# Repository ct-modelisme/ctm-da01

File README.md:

# CTM-DA01: Digital Sound Decoder 01

The CTM-DA01 is a sound module for modelrailway projects.
This sound module is compatible with DCC & DC train layouts.

## Licenses

The hardware is released under OpenHardware principes, and the software under OpenSource principes.

 - Hardware (PCB): [Creative Commons Attribution-ShareAlike 4.0 International License](http://creativecommons.org/licenses/by-sa/4.0/)
 - Software (Firmware): [GNU General Public License v3](https://www.gnu.org/licenses/)

## Current releases

 - Hardware (PCB): version 1.0
 - Software (Firmware): version 1.1

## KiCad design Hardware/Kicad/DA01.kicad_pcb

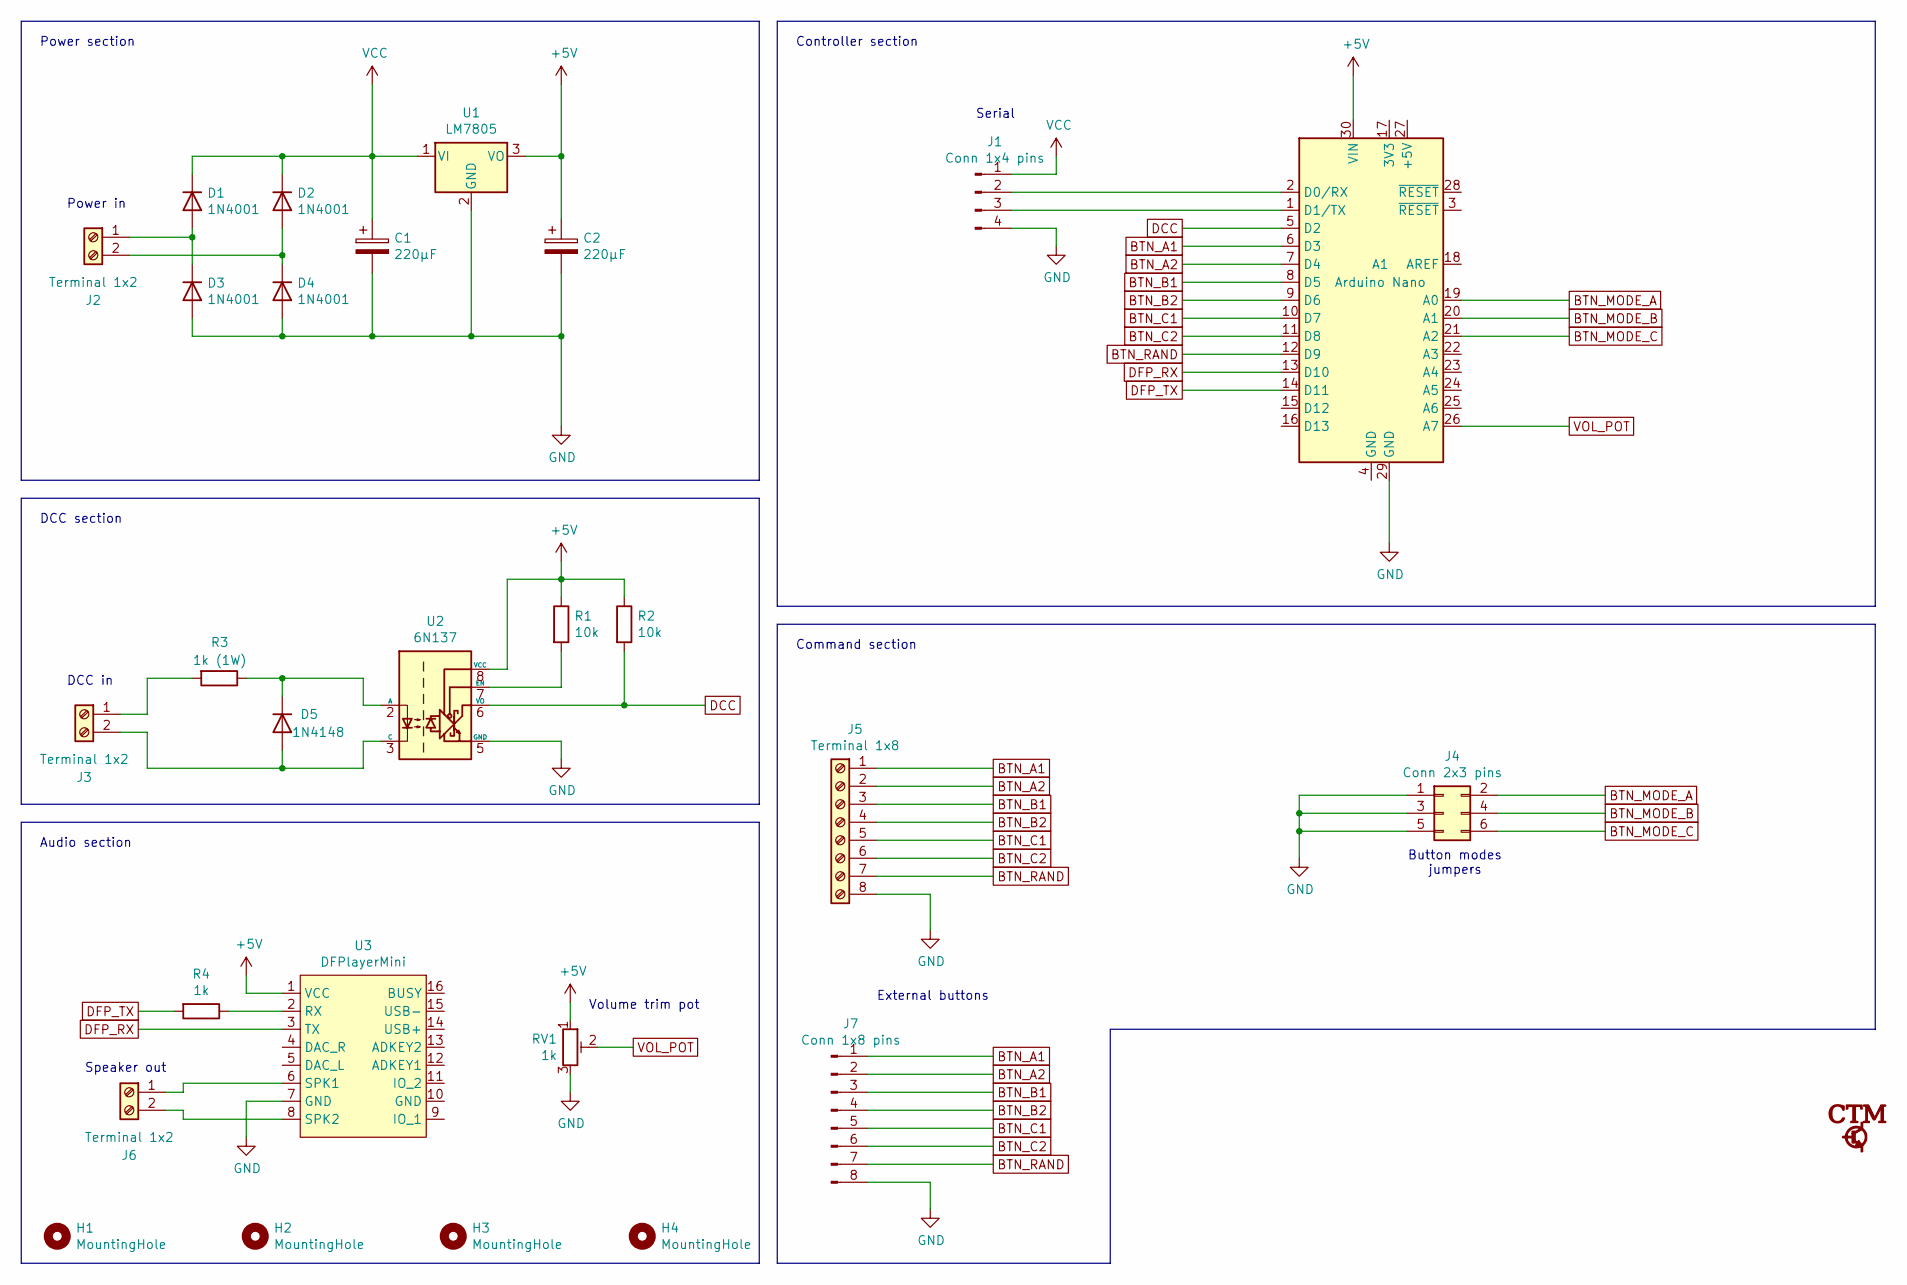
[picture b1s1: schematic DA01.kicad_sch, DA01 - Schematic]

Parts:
A1: Arduino Nano; Arduino_Nano
C1, C2: 220µF; CP_Radial_D6.3mm_P2.50mm
D1, D2, D3, D4: 1N4001; D_DO-41_SOD81_P10.16mm_Horizontal
D5: 1N4148; D_DO-35_SOD27_P7.62mm_Horizontal
H1, H2, H3, H4: MountingHole; MountingHole_3.2mm_M3
J1: Conn 1x4 pins; PinHeader_1x04_P2.54mm_Vertical
J2, J3, J6: Terminal 1x2; TerminalBlock_bornier-2_P5.08mm
J4: Conn 2x3 pins; PinHeader_2x03_P2.54mm_Vertical
J5: Terminal 1x8; TerminalBlock_bornier-8_P5.08mm
J7: Conn 1x8 pins; PinHeader_1x08_P2.54mm_Vertical
R1, R2: 10k; R_Axial_DIN0207_L6.3mm_D2.5mm_P10.16mm_Horizontal
R3: 1k (1W); R_Axial_DIN0309_L9.0mm_D3.2mm_P12.70mm_Horizontal
R4: 1k; R_Axial_DIN0207_L6.3mm_D2.5mm_P10.16mm_Horizontal
RV1: 1k; Potentiometer_ACP_CA9-H2,5_Horizontal
U1: LM7805; TO-220-3_Vertical
U2: 6N137; DIP-8_W7.62mm
U3: DFPlayerMini; DFRobot_DFPlayerMini_DFR0299

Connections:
+5V: A1.30 (VIN), C2.1, R1.1, R2.1, RV1.1, U1.3 (VO), U2.8 (VCC), U3.1 (VCC)
BTN_A1: A1.6 (D3), J5.1, J7.1
BTN_A2: A1.7 (D4), J5.2, J7.2
BTN_B1: A1.8 (D5), J5.3, J7.3
BTN_B2: A1.9 (D6), J5.4, J7.4
BTN_C1: A1.10 (D7), J5.5, J7.5
BTN_C2: A1.11 (D8), J5.6, J7.6
BTN_MODE_A: A1.19 (A0), J4.2
BTN_MODE_B: A1.20 (A1), J4.4
BTN_MODE_C: A1.21 (A2), J4.6
BTN_RAND: A1.12 (D9), J5.7, J7.7
DCC: A1.5 (D2), R2.2, U2.6 (VO)
DFP_RX: A1.13 (D10), U3.3 (TX)
DFP_TX: A1.14 (D11), R4.2
GND: A1.29 (GND), C1.2, C2.2, D3.2 (A), D4.2 (A), J1.4, J4.1, J4.3, J4.5, J5.8, J7.8, RV1.3, U1.2 (GND), U2.5 (GND), U3.7 (GND)
unnamed: A1.1 (D1/TX), J1.3
unnamed: A1.2 (D0/RX), J1.2
unnamed: D1.2 (A), D3.1 (K), J2.1
unnamed: D2.2 (A), D4.1 (K), J2.2
unnamed: D5.1 (K), R3.1, U2.2 (A)
unnamed: D5.2 (A), J3.2, U2.3 (C)
unnamed: J3.1, R3.2
unnamed: J6.1, U3.6 (SPK1)
unnamed: J6.2, U3.8 (SPK2)
unnamed: R1.2, U2.7 (EN)
unnamed: R4.1, U3.2 (RX)
VCC: C1.1, D1.1 (K), D2.1 (K), J1.1, U1.1 (VI)
VOL_POT: A1.26 (A7), RV1.2

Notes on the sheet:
Volume trim pot
DCC in
Power section
DCC section
Button modes jumpers
Command section
Serial
Power in
Speaker out
Audio section
External buttons
Controller section

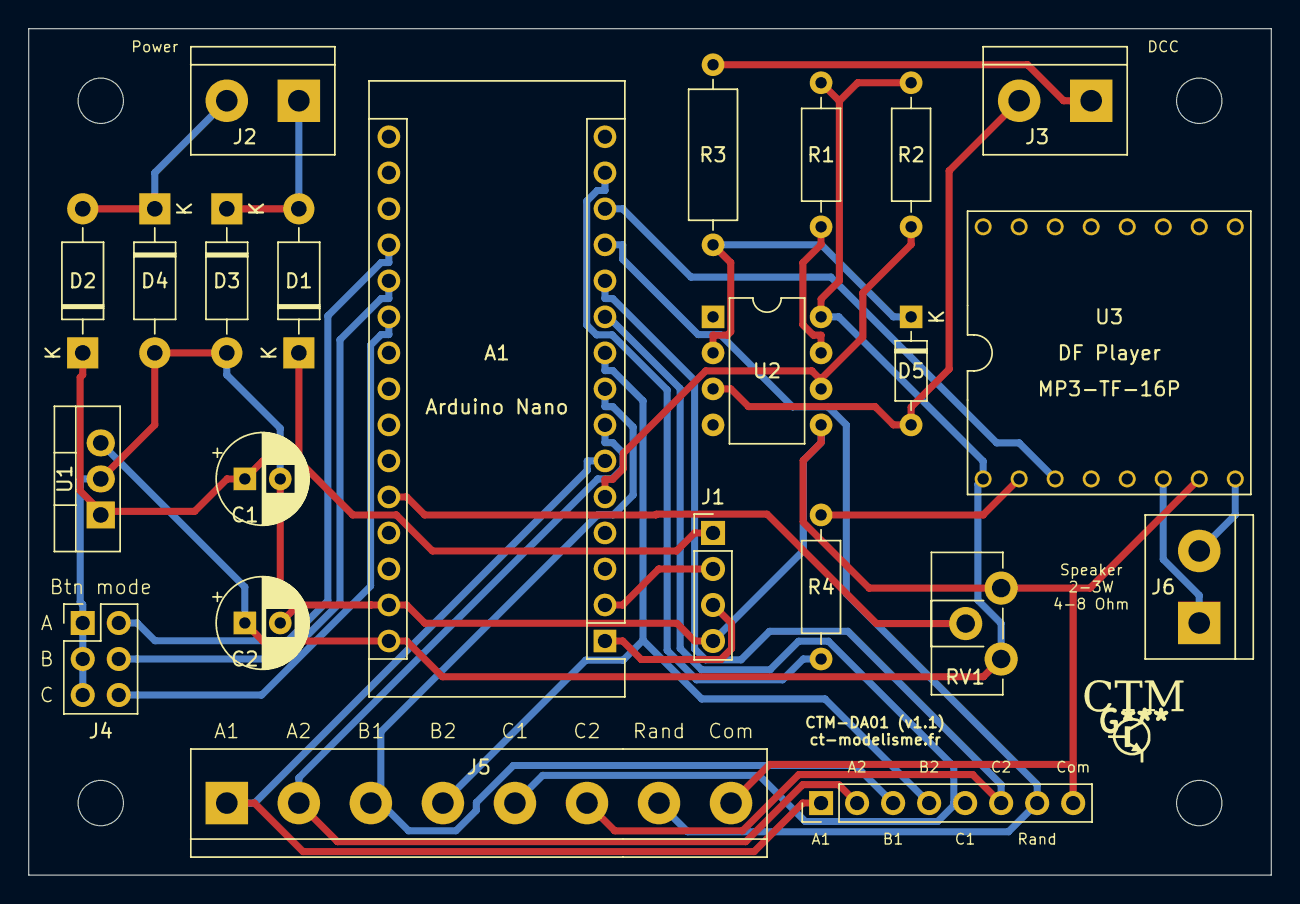
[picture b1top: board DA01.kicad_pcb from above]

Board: 2 copper layers, 87.6 x 59.7 mm, 27 parts (0 on the bottom side), 28 nets.

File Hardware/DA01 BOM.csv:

"Source:","/home/iwa/documents/KiCAD/Digital Accessory Decoder/DAD 02/DAD 02/DAD 02.sch"
"Date:","Mon 23 Aug 2021 12:42:14 PM CEST"
"Tool:","Eeschema 5.1.10"
"Generator:","/usr/share/kicad/plugins/bom_csv_grouped_by_value.py"
"Component Count:","27"

"Individual Components:"

"Item","Qty","Reference(s)","Value","LibPart","Footprint","Datasheet"
"","","A1","Arduino Nano","MCU_Module:Arduino_Nano_v2.x","Module:Arduino_Nano","https://www.arduino.cc/en/uploads/Main/ArduinoNanoManual23.pdf"
"","","C1","220µF","Device:C_Polarized","Capacitor_THT:CP_Radial_D6.3mm_P2.50mm","~"
"","","C2","220µF","Device:C_Polarized","Capacitor_THT:CP_Radial_D6.3mm_P2.50mm","~"
"","","D1","1N4001","Diode:1N4001","Diode_THT:D_DO-41_SOD81_P10.16mm_Horizontal","http://www.vishay.com/docs/88503/1n4001.pdf"
"","","D2","1N4001","Diode:1N4001","Diode_THT:D_DO-41_SOD81_P10.16mm_Horizontal","http://www.vishay.com/docs/88503/1n4001.pdf"
"","","D3","1N4001","Diode:1N4001","Diode_THT:D_DO-41_SOD81_P10.16mm_Horizontal","http://www.vishay.com/docs/88503/1n4001.pdf"
"","","D4","1N4001","Diode:1N4001","Diode_THT:D_DO-41_SOD81_P10.16mm_Horizontal","http://www.vishay.com/docs/88503/1n4001.pdf"
"","","D5","1N4148","Diode:1N4148","Diode_THT:D_DO-35_SOD27_P7.62mm_Horizontal","https://assets.nexperia.com/documents/data-sheet/1N4148_1N4448.pdf"
"","","H1","MountingHole","Mechanical:MountingHole","MountingHole:MountingHole_3.2mm_M3","~"
"","","H2","MountingHole","Mechanical:MountingHole","MountingHole:MountingHole_3.2mm_M3","~"
"","","H3","MountingHole","Mechanical:MountingHole","MountingHole:MountingHole_3.2mm_M3","~"
"","","H4","MountingHole","Mechanical:MountingHole","MountingHole:MountingHole_3.2mm_M3","~"
"","","J1","Conn 1x4 pins","Connector:Conn_01x04_Male","Connector_PinHeader_2.54mm:PinHeader_1x04_P2.54mm_Vertical","~"
"","","J2","Terminal 1x2","Connector:Screw_Terminal_01x02","TerminalBlock:TerminalBlock_bornier-2_P5.08mm","~"
"","","J3","Terminal 1x2","Connector:Screw_Terminal_01x02","TerminalBlock:TerminalBlock_bornier-2_P5.08mm","~"
"","","J4","Conn 2x3 pins","Connector_Generic:Conn_02x03_Odd_Even","Connector_PinHeader_2.54mm:PinHeader_2x03_P2.54mm_Vertical","~"
"","","J5","Terminal 1x8","Connector:Screw_Terminal_01x08","TerminalBlock:TerminalBlock_bornier-8_P5.08mm","~"
"","","J6","Terminal 1x2","Connector:Screw_Terminal_01x02","TerminalBlock:TerminalBlock_bornier-2_P5.08mm","~"
"","","J7","Conn 1x8 pins","Connector:Conn_01x08_Male","Connector_PinHeader_2.54mm:PinHeader_1x08_P2.54mm_Vertical","~"
"","","R1","10k","Device:R","Resistor_THT:R_Axial_DIN0207_L6.3mm_D2.5mm_P10.16mm_Horizontal","~"
"","","R2","10k","Device:R","Resistor_THT:R_Axial_DIN0207_L6.3mm_D2.5mm_P10.16mm_Horizontal","~"
"","","R3","1k (1W)","Device:R","Resistor_THT:R_Axial_DIN0309_L9.0mm_D3.2mm_P12.70mm_Horizontal","~"
"","","R4","1k","Device:R","Resistor_THT:R_Axial_DIN0207_L6.3mm_D2.5mm_P10.16mm_Horizontal","~"
"","","RV1","1k","Device:R_Potentiometer_Trim","Potentiometer_THT:Potentiometer_ACP_CA9-H2,5_Horizontal","~"
"","","U1","LM7805","Regulator_Linear:LM7805_TO220","Package_TO_SOT_THT:TO-220-3_Vertical","https://www.onsemi.cn/PowerSolutions/document/MC7800-D.PDF"
"","","U2","6N137","Isolator:6N137","Package_DIP:DIP-8_W7.62mm","https://docs.broadcom.com/docs/AV02-0940EN"
"","","U3","DFPlayerMini","DAD-02-rescue:DFPlayerMini-Audio","Module:DFRobot_DFPlayerMini_DFR0299","https://wiki.dfrobot.com/DFPlayer_Mini_SKU_DFR0299"



"Collated Components:"

"Item","Qty","Reference(s)","Value","LibPart","Footprint","Datasheet"
"1","1","A1","Arduino Nano","MCU_Module:Arduino_Nano_v2.x","Module:Arduino_Nano","https://www.arduino.cc/en/uploads/Main/ArduinoNanoManual23.pdf"
"2","2","C1, C2","220µF","Device:C_Polarized","Capacitor_THT:CP_Radial_D6.3mm_P2.50mm","~"
"3","4","D1, D2, D3, D4","1N4001","Diode:1N4001","Diode_THT:D_DO-41_SOD81_P10.16mm_Horizontal","http://www.vishay.com/docs/88503/1n4001.pdf"
"4","1","D5","1N4148","Diode:1N4148","Diode_THT:D_DO-35_SOD27_P7.62mm_Horizontal","https://assets.nexperia.com/documents/data-sheet/1N4148_1N4448.pdf"
"5","4","H1, H2, H3, H4","MountingHole","Mechanical:MountingHole","MountingHole:MountingHole_3.2mm_M3","~"
"6","1","J1","Conn 1x4 pins","Connector:Conn_01x04_Male","Connector_PinHeader_2.54mm:PinHeader_1x04_P2.54mm_Vertical","~"
"7","3","J2, J3, J6","Terminal 1x2","Connector:Screw_Terminal_01x02","TerminalBlock:TerminalBlock_bornier-2_P5.08mm","~"
"8","1","J4","Conn 2x3 pins","Connector_Generic:Conn_02x03_Odd_Even","Connector_PinHeader_2.54mm:PinHeader_2x03_P2.54mm_Vertical","~"
"9","1","J5","Terminal 1x8","Connector:Screw_Terminal_01x08","TerminalBlock:TerminalBlock_bornier-8_P5.08mm","~"
"10","1","J7","Conn 1x8 pins","Connector:Conn_01x08_Male","Connector_PinHeader_2.54mm:PinHeader_1x08_P2.54mm_Vertical","~"
"11","2","R1, R2","10k","Device:R","Resistor_THT:R_Axial_DIN0207_L6.3mm_D2.5mm_P10.16mm_Horizontal","~"
"12","1","R3","1k (1W)","Device:R","Resistor_THT:R_Axial_DIN0309_L9.0mm_D3.2mm_P12.70mm_Horizontal","~"
"13","1","R4","1k","Device:R","Resistor_THT:R_Axial_DIN0207_L6.3mm_D2.5mm_P10.16mm_Horizontal","~"
"14","1","RV1","1k","Device:R_Potentiometer_Trim","Potentiometer_THT:Potentiometer_ACP_CA9-H2,5_Horizontal","~"
"15","1","U1","LM7805","Regulator_Linear:LM7805_TO220","Package_TO_SOT_THT:TO-220-3_Vertical","https://www.onsemi.cn/PowerSolutions/document/MC7800-D.PDF"
"16","1","U2","6N137","Isolator:6N137","Package_DIP:DIP-8_W7.62mm","https://docs.broadcom.com/docs/AV02-0940EN"
"17","1","U3","DFPlayerMini","DAD-02-rescue:DFPlayerMini-Audio","Module:DFRobot_DFPlayerMini_DFR0299","https://wiki.dfrobot.com/DFPlayer_Mini_SKU_DFR0299"

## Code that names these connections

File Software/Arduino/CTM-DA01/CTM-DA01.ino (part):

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

// Constants
#define BTN_MODE_A_PIN A0                                       // The pin connected to "MODE A" jumpers
#define BTN_MODE_B_PIN A1                                       // The pin connected to "MODE B" jumpers
#define BTN_MODE_C_PIN A2                                       // The pin connected to "MODE C" jumpers
#define VOL_TRIM_PIN   A7                                       // The pin connected to volume trim pot
#define DCC_SIGNAL_PIN 2                                        // The pin connected to opto-isolator
#define BTN_A1_PIN     3                                        // The pin connected to button "A1"
#define BTN_A2_PIN     4                                        // The pin connected to button "A2"
#define BTN_B1_PIN     5                                        // The pin connected to button "B1"
#define BTN_B2_PIN     6                                        // The pin connected to button "B2"
#define BTN_C1_PIN     7                                        // The pin connected to button "C1"
#define BTN_C2_PIN     8                                        // The pin connected to button "C2"
#define BTN_RAND_PIN   9                                        // The pin connected to button "RAND"
#define PLAYER_RX_PIN  10                                       // The pin connected to serial rx of DFPlayer
#define PLAYER_TX_PIN  11                                       // The pin connected to serial tx of DFPlayer

#define DECODER_VERSION 1                                       // The decoder version used by NmraDcc lib
#define FACTORY_DCC_ADDRESS 3                                   // The default DCC address for this decoder


// Structures
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void
processButtons()
{
  int modeA = digitalRead(BTN_MODE_A_PIN);
  int modeB = digitalRead(BTN_MODE_B_PIN);
  int modeC = digitalRead(BTN_MODE_C_PIN);

  if(!digitalRead(BTN_RAND_PIN))
  {
    playRandomSong();
  }
  else if(!digitalRead(BTN_A1_PIN))
  {
    if(modeA)
      playSimpleSong(1);
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      playLoopingSong(1);

    // Software anti-rebound
    do delay(200); while(!digitalRead(BTN_A1_PIN));
  }
  else if(!digitalRead(BTN_A2_PIN))
  {
    if(modeA)
      playSimpleSong(2);
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      playLoopingSong(2);

    // Software anti-rebound
    do delay(200); while(!digitalRead(BTN_A2_PIN));
  }
  else if(!digitalRead(BTN_B1_PIN))
  {
    if(modeA && modeB)
      playSimpleSong(3);
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      playLoopingSong(3);

    // Software anti-rebound
    do delay(200); while(!digitalRead(BTN_B1_PIN));
  }
  else if(!digitalRead(BTN_B2_PIN))
  {
    if(modeA && modeB)
      playSimpleSong(4);
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      playLoopingSong(4);

    // Software anti-rebound
    do delay(200); while(!digitalRead(BTN_B2_PIN));
  }
  else if(!digitalRead(BTN_C1_PIN))
  {
    if(modeA)
    {
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    }

    // Software anti-rebound
    do delay(200); while(!digitalRead(BTN_C1_PIN));
  }
  else if(!digitalRead(BTN_C2_PIN))
  {
    if(modeA)
    {
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    }

    // Software anti-rebound
    do delay(200); while(!digitalRead(BTN_C2_PIN));
  }
}

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  Serial.println("Initializing microcontroller...");
  Serial.println(" - Serial communication initialized");

  pinMode(BTN_MODE_A_PIN, INPUT_PULLUP);
  pinMode(BTN_MODE_B_PIN, INPUT_PULLUP);
  pinMode(BTN_MODE_C_PIN, INPUT_PULLUP);
  pinMode(BTN_A1_PIN, INPUT_PULLUP);
  pinMode(BTN_A2_PIN, INPUT_PULLUP);
  pinMode(BTN_B1_PIN, INPUT_PULLUP);
  pinMode(BTN_B2_PIN, INPUT_PULLUP);
  pinMode(BTN_C1_PIN, INPUT_PULLUP);
  pinMode(BTN_C2_PIN, INPUT_PULLUP);
  pinMode(BTN_RAND_PIN, INPUT_PULLUP);

  Serial.println(" - Inputs/Outputs initialized");
  Serial.println("\nInitializing audio driver...");
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  Serial.println(" - MP3-TF-16P driver configured");
  Serial.println("\nInitializing DCC decoder...");

  dcc.pin(0, DCC_SIGNAL_PIN, 0);
  dcc.init(MAN_ID_DIY, DECODER_VERSION, FLAGS_AUTO_FACTORY_DEFAULT, 0);

  Serial.print(" - Short DCC address: ");
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
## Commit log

2022-02-20 Public release of DAD-02
2022-02-20 Extract the v1.0 of PCB
2022-02-20 README notice
2022-02-20 Public release of firmware v1.1
2022-02-20 Move documentation to separated folder
2022-08-01 Rename projet from DAD-02 to CTM-DA01
2022-08-01 Refactoring
2022-08-02 Kicad refactoring
2022-08-02 Clean
2023-07-31 Some renaming
2024-02-17 Refactoring and documentation
2024-02-17 Add CTM in cartridge & PCB

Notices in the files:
Software/Arduino/CTM-DA01/CTM-DA01.ino:
This program is free software: you can redistribute it and/or modify
it under the terms of the GNU General Public License as published by
the Free Software Foundation, either version 3 of the License, or
(at your option) any later version.
